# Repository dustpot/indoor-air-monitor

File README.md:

# Indoor Air Monitor

A battery-powered ESP32 monitor for the non-particulate parts of indoor air: temperature, humidity, pressure, eCO₂, and TVOC. It combines the readings into three 0–100 scores (Asthma, Sleep, and Freshness), shows them on a 20×4 LCD, and logs them to ThingSpeak over WiFi.

Built for ELEE 4230 (Sensors and Transducers) at the University of Georgia, 2026. Solo project.

## Hardware

| Part | Role |
| --- | --- |
| ESP32 dev board | Microcontroller, WiFi, touch input, 12-bit ADC |
| 10 kΩ NTC thermistor | Raw temperature sensor with a custom analog front end |
| BME280 | Temperature, humidity, pressure (I²C, 0x76) |
| SGP30 | eCO₂ and TVOC (I²C, 0x58) |
| Copper-tape pad | Homemade capacitive touch input on GPIO27 |
| 20×4 LCD with I²C backpack | Display and menu |
| 6×AA NiMH + LM2596 buck | Power, regulated to 5.0 V |

Total parts cost was about $88.

## Thermistor front end

The thermistor goes through a parallel resistor (7.46 kΩ) to linearize it, a bias divider, a TL071 gain stage (gain ≈ 8.7, referenced to 3.5 V, with low-pass filtering), and a ×0.40 divider so the ADC never sees more than 3.3 V. It's read on GPIO32, because the ESP32's second ADC is disabled while WiFi is on.

- Calibrated with 80 resistance-temperature readings from 1.3 to 61 °C: β = 3992 K, R₂₅ = 10.21 kΩ, R² = 0.9995
- A 1-D Kalman filter at 5 Hz (Q = 0.0008, R = 0.15) cut sample-to-sample noise from ±0.42 °C to ±0.02 °C
- Agrees with the BME280 to within 0.55 °C on average (1.22 °C worst case) over 12 minutes

## Scores

Each measurement gets a 0–100 subscore based on how close it is to an ideal range. Each index is a weighted average of its four subscores.

| Measurement | Asthma weight | Sleep weight | Freshness weight |
| --- | --- | --- | --- |
| TVOC | 0.35 | 0.10 | 0.45 |
| eCO₂ | 0.25 | 0.25 | 0.45 |
| Temperature | 0.20 | 0.35 | 0.05 |
| Humidity | 0.20 | 0.30 | 0.05 |

Above 79 is Good, 50–79 is Average, below 50 is Poor.

Moving the unit from my bedroom to the kitchen after cooking:

| Index | Bedroom | Kitchen | Change |
| --- | --- | --- | --- |
| Asthma | 86 | 39 | −47 |
| Sleep | 65 | 44 | −21 |
| Freshness | 97 | 53 | −44 |

## Controls

The copper pad is the only input. Tap to cycle, hold for 1.5 s to select or go back. Menus: Asthma, Sleep, Freshness, and raw measurements.

## Repository layout

```
indoor-air-monitor/
├── README.md
├── firmware/
│   └── airquality.ino
├── hardware/
│   ├── kicad/              # .kicad_pro, .kicad_sch, .kicad_pcb
│   └── schematic.pdf
├── data/
└── docs/
    ├── report.pdf
    ├── BOM.md
    └── images/
```

## Building

1. Install the Arduino IDE with ESP32 board support.
2. Install the Adafruit BME280, Adafruit SGP30, LiquidCrystal_I2C, and ThingSpeak libraries.
3. Put your WiFi credentials and ThingSpeak API key in `firmware/secrets.h` (not committed).
4. Upload `airquality.ino` to the ESP32.

## Limitations

- The SGP30 reports changes relative to a baseline, not true concentrations. eCO₂ is an estimate, not a real CO₂ measurement.
- The Sleep index can't go above 65 when the room is 23 °C or warmer, because the temperature subscore drops to zero there.

## Documentation

Full report: [docs/report.pdf](docs/report.pdf)

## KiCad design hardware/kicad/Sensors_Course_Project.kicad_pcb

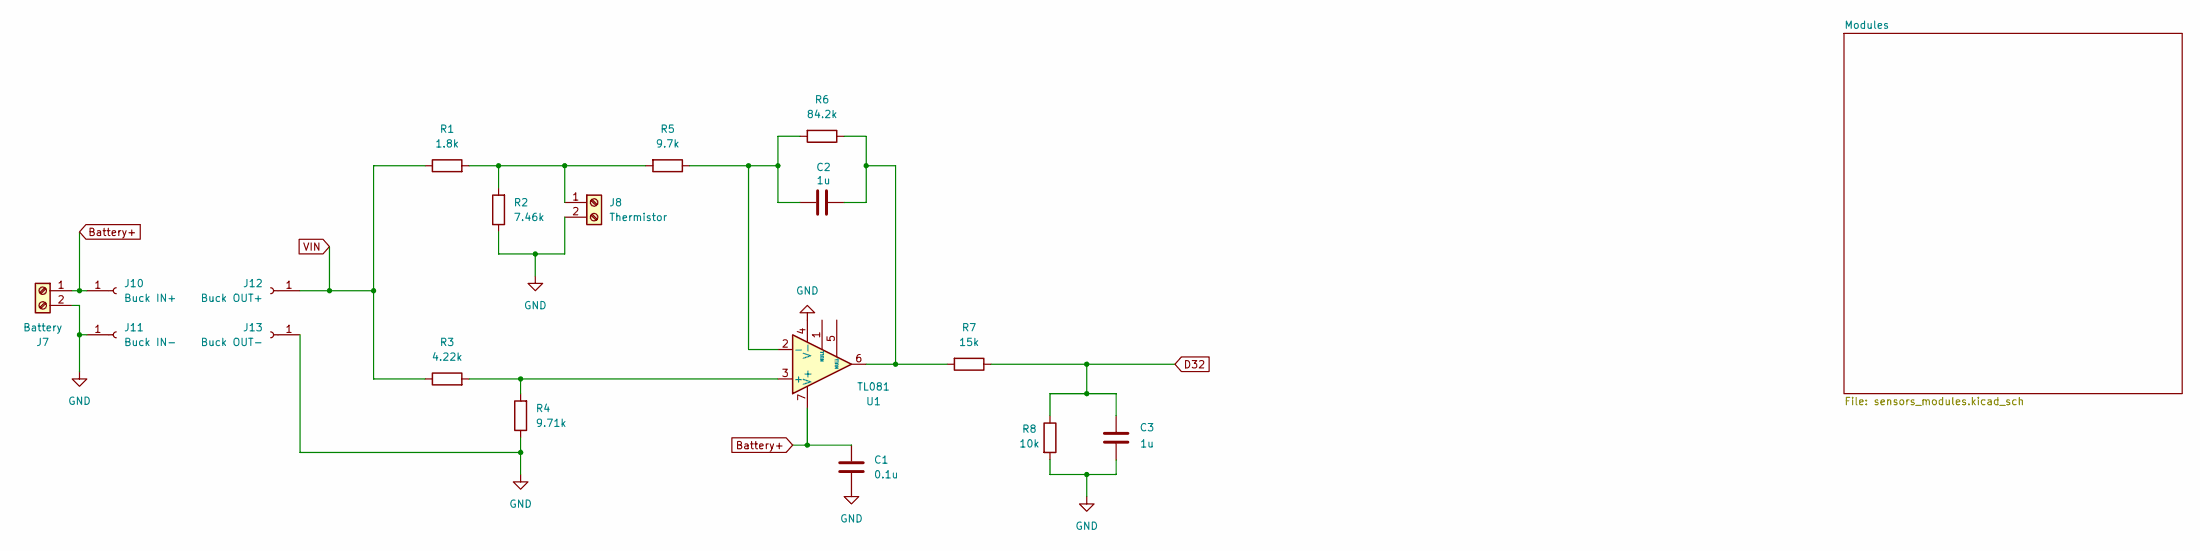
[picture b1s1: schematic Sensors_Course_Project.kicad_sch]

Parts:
C1: 0.1u; C_Disc_D5.0mm_W2.5mm_P2.50mm
C2, C3: 1u; CP_Radial_D5.0mm_P2.00mm
J7: Battery; TerminalBlock_Phoenix_MKDS-1,5-2-5.08_1x02_P5.08mm_Horizont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
J8: Thermistor; TerminalBlock_Phoenix_MKDS-1,5-2-5.08_1x02_P5.08mm_Horizont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
J10: Buck IN+; PinSocket_1x01_P2.54mm_Vertical
J11: Buck IN-; PinSocket_1x01_P2.54mm_Vertical
J12: Buck OUT+; PinSocket_1x01_P2.54mm_Vertical
J13: Buck OUT-; PinSocket_1x01_P2.54mm_Vertical
R1: 1.8k; R_Axial_DIN0207_L6.3mm_D2.5mm_P7.62mm_Horizontal
R2: 7.46k; R_Axial_DIN0207_L6.3mm_D2.5mm_P7.62mm_Horizontal
R3: 4.22k; R_Axial_DIN0207_L6.3mm_D2.5mm_P7.62mm_Horizontal
R4: 9.71k; R_Axial_DIN0207_L6.3mm_D2.5mm_P7.62mm_Horizontal
R5: 9.7k; R_Axial_DIN0207_L6.3mm_D2.5mm_P7.62mm_Horizontal
R6: 84.2k; R_Axial_DIN0207_L6.3mm_D2.5mm_P7.62mm_Horizontal
R7: 15k; R_Axial_DIN0207_L6.3mm_D2.5mm_P7.62mm_Horizontal
R8: 10k; R_Axial_DIN0207_L6.3mm_D2.5mm_P7.62mm_Horizontal
U1: TL081; DIP-8_W7.62mm

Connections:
Battery+: C1.1, J7.1, J10.1, U1.7 (V+)
D32: C3.2, R7.1, R8.1; also elsewhere on the board
GND: C1.2, C3.1, J7.2, J8.2, J11.1, J13.1, R2.1, R4.1, R8.2, U1.4 (V-); also elsewhere on the board
unnamed: C2.2, R6.1, R7.2, U1.6
unnamed: J8.1, R1.2, R2.2, R5.2
unnamed: R3.2, R4.2, U1.3 (+)
unnamed: C2.1, R5.1, R6.2, U1.2 (-)
VIN: J12.1, R1.1, R3.1; also elsewhere on the board

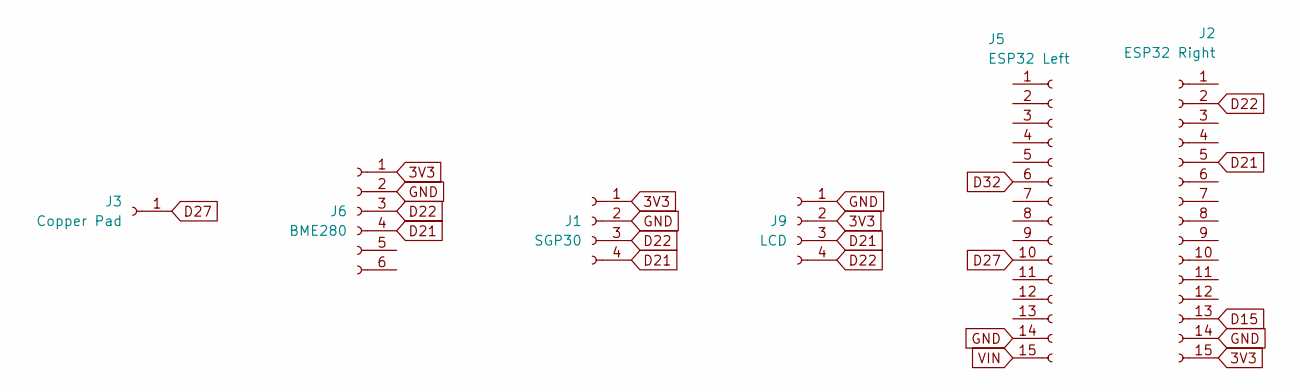
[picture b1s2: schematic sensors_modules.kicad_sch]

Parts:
J1: SGP30; PinSocket_1x04_P2.54mm_Vertical
J2: ESP32 Right; PinSocket_1x15_P2.54mm_Vertical
J3: Copper Pad; JST_XH_B1B-XH-AM_1x01_P2.50mm_Vertical
J5: ESP32 Left; PinSocket_1x15_P2.54mm_Vertical
J6: BME280; PinSocket_1x06_P2.54mm_Vertical
J9: LCD; PinSocket_1x04_P2.54mm_Vertical

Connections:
3V3: J1.1, J2.15, J6.1, J9.2
D15: J2.13
D21: J1.4, J2.5, J6.4, J9.3
D22: J1.3, J2.2, J6.3, J9.4
D27: J3.1, J5.10
D32: J5.6; also elsewhere on the board
GND: J1.2, J2.14, J5.14, J6.2, J9.1; also elsewhere on the board
VIN: J5.15; also elsewhere on the board

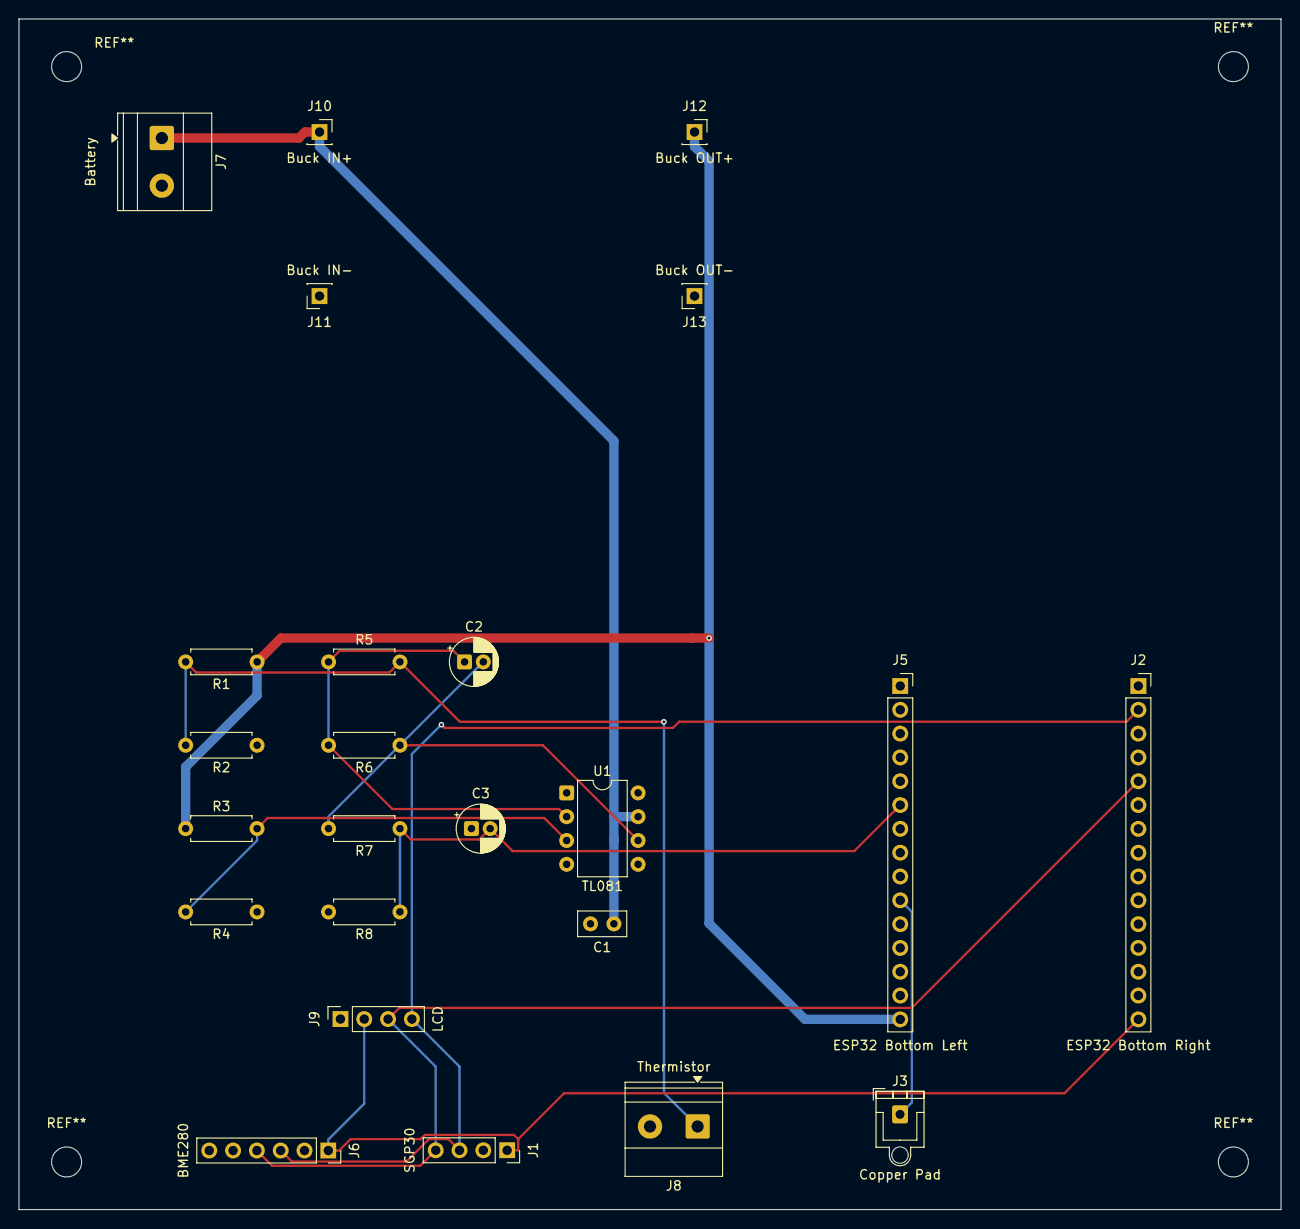
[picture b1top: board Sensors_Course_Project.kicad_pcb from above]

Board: 2 copper layers, 134.6 x 127.0 mm, 24 parts (0 on the bottom side), 12 nets.
